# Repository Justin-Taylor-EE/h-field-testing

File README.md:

# h-field-testing
X-Y cartesian machine for measuring H-field emissions.

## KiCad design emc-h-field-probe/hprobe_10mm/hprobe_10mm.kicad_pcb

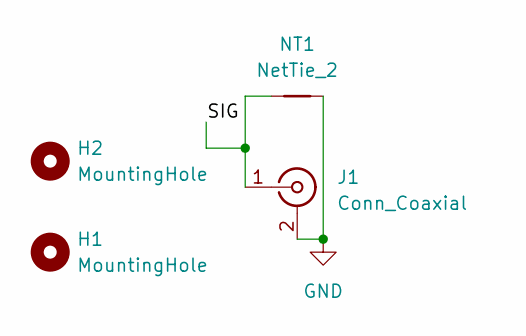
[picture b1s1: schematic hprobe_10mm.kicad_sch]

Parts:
H1, H2: MountingHole; MountingHole_3.2mm_M3
J1: Conn_Coaxial; SMA_Amphenol_901-144_Vertical
NT1: NetTie_2; NetTie-2_SMD_Pad0.5mm

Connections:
/SIG: J1.1 (In), NT1.1
GND: J1.2 (Ext), NT1.2

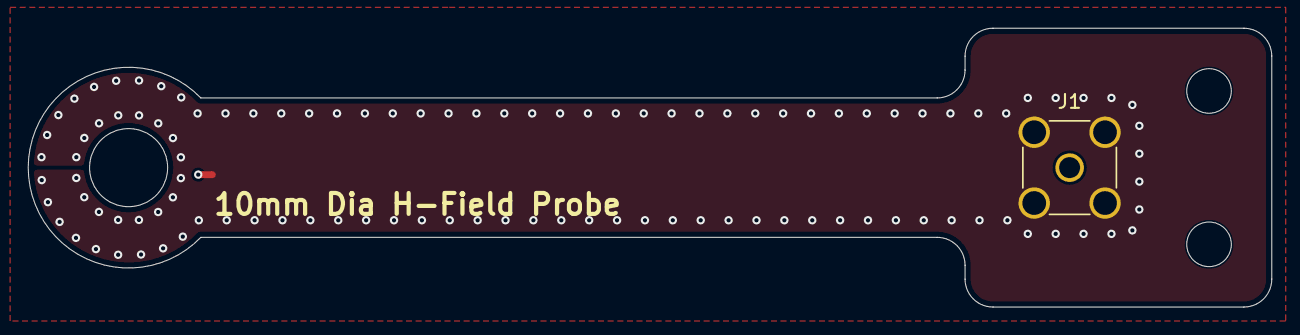
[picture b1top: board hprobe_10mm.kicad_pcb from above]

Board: 4 copper layers, 89.2 x 20.0 mm, 4 parts (0 on the bottom side), 2 nets.
